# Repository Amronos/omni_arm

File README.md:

# Omni Arm

**_This is a work in progress and not usable currently._**

A universal robot arm featuring 3 robot grippers (parallel jaw, suction cup, and jamming) and 9 DOFS (including 3 for each gripper), allowing it to pickup objects of any kind as long as they have reasonable size and weight.

## Features

- 1 DOF for rotation on the x-axis.
- 3 DOFs for rotation on the y-axis.
- 2 DOFs for rotation on the z-axis.
- 3 different grippers: parallel jaw, suction cup, and jamming.
- Can pickup objects of any kind as long as they are of reasonable weight and size (size is not a limit for the suction cup gripper).
- Precise arm position control alongside position, velocity, load, and input voltage feedback from Waveshare servo motors.
- [ROS 2](https://docs.ros.org) support that uses [MoveIt 2](https://moveit.ai). (Coming Soon)

## Why Create This?

There are hardly any open-source and low-cost robot arms available out there that allow you to pikcup all sorts of objects with the use of various grippers.<br>
Most of the avilable robot arms also don't offer the kind of feedback and control one needs on the motors to perform complex kinematics and dynamics.<br>
This robot arm does all of that, making it perfect for my use-cases.

## Images

## Wiring Diagram

## BOM

| Item                                    | Unit Price | Quantity | Total Price | Links                                                                     |
| --------------------------------------- | ---------- | -------- | ----------- | ------------------------------------------------------------------------- |
| Waveshare SC15 Servo                    | $17.99     | 4        | $71.96      | https://www.waveshare.com/sc15-servo.htm                                  |
| Waveshare SC09 Servo                    | $8.99      | 4        | $35.96      | https://www.waveshare.com/sc09-servo.htm                                  |
| PCB                                     | $43.77     | 2        | $43.77      | https://jlpcb.com/                                                        |
| Xiao ESP32-C3                           | $5.71      | 1        | $5.71       | https://thinkrobotics.com/products/seeed-studio-xiao-esp32c3              |
| Dispo Van 20 ml Plastic Syringe         | $0.23      | 1        | $0.23       | https://www.amazon.in/DISPO-Plastic-Syringe-Medical-Purpose/dp/B09KS18BMY |
| Suction Cup Gripper for DIY Robot Arms  | $27.85     | 1        | $27.85      | https://thinkrobotics.com/products/suction-cup-gripper-for-diy-robot-arms |
| M2x9.5 Pan Head Self Tapping Screw      | —          | 10       | —           | —                                                                         |
| M2x6.5 Pan Head Self Tapping Screw      | —          | 10       | —           | —                                                                         |
| M3x8 Pan Head Self Tapping Screw        | —          | 4        | —           | —                                                                         |
| M3x10 Pan Head Self Tapping Screw       | —          | 2        | —           | —                                                                         |
| 2x50mm Stainless Steel Round Shaft Rods | —          | 2        | —           | —                                                                         |
| 3D Prints                               | —          | 1        | —           | https://github.com/Amronos/omni_arm/tree/main/CAD                         |
|                                         |            |          | $185.48     |                                                                           |

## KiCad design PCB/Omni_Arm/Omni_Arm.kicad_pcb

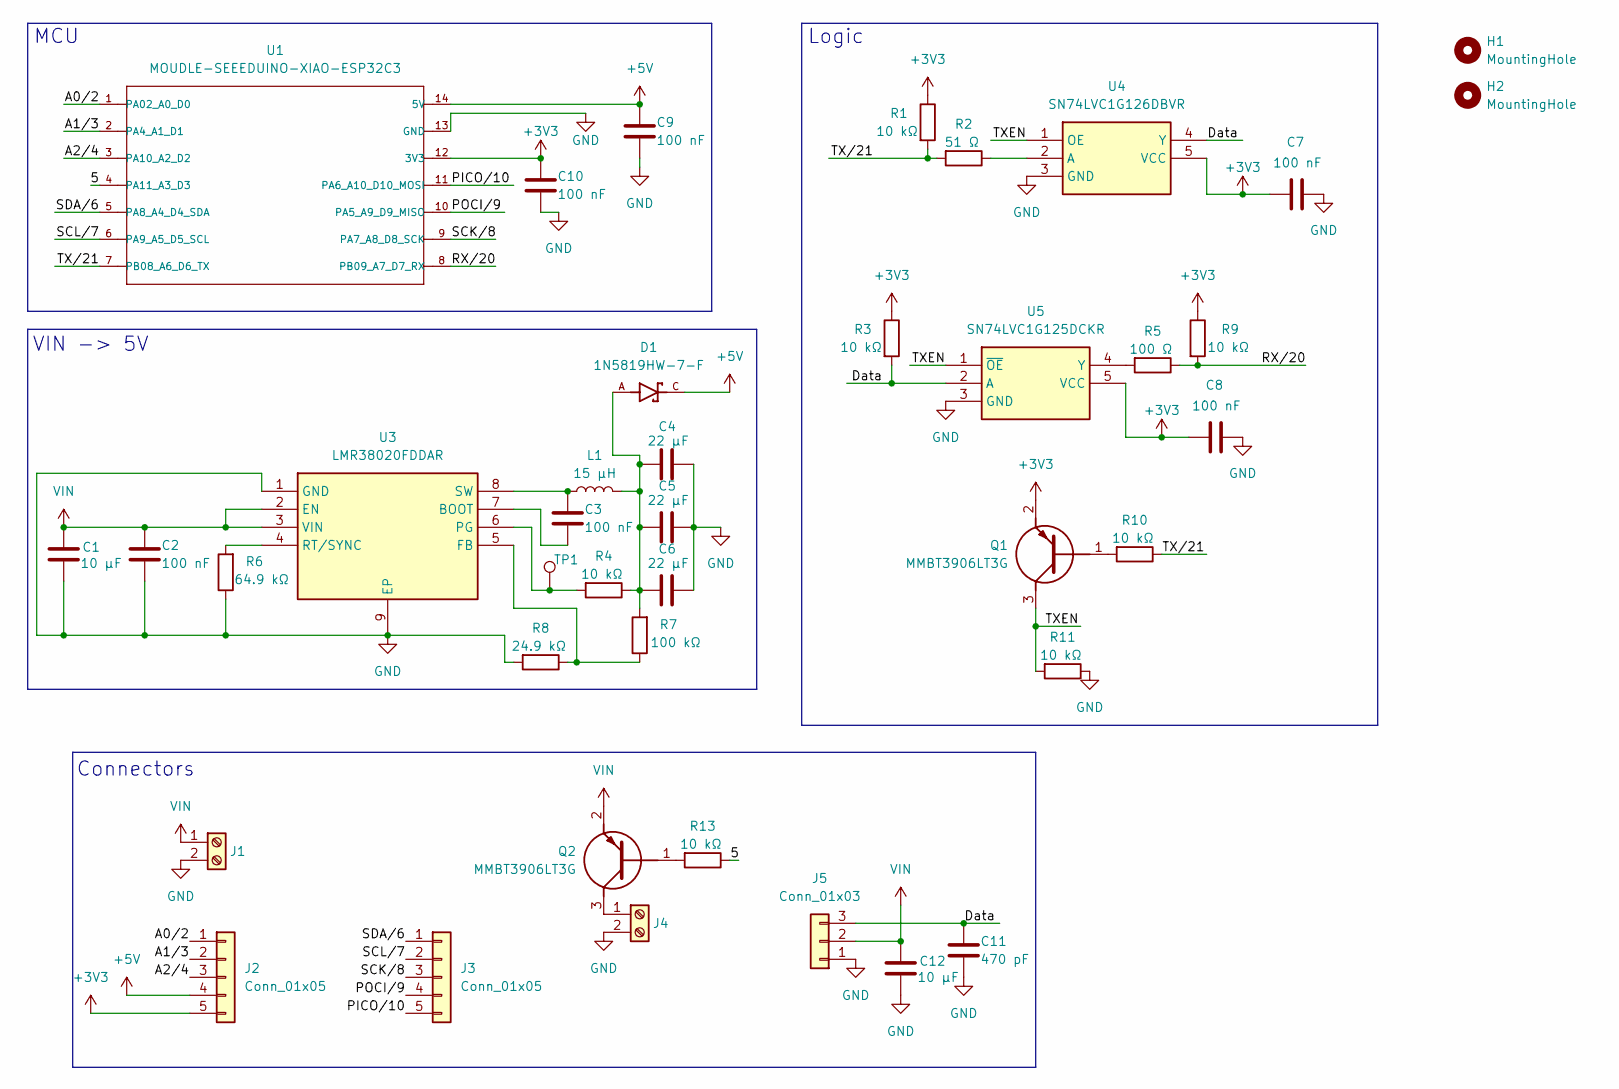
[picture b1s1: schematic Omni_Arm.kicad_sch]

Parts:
C1, C12: 10 µF; C_0805_2012Metric
C2, C3, C7, C8, C9, C10: 100 nF; C_0402_1005Metric
C4, C5, C6: 22 µF; C_0603_1608Metric
C11: 470 pF; C_0402_1005Metric
D1: 1N5819HW-7-F; SOD3715X145N
H1, H2: MountingHole; MountingHole_3.2mm_M3
J1, J4: Screw_Terminal_01x02; TerminalBlock_Xinya_XY308-2.54-2P_1x02_P2.54mm_Horizontal
J2, J3: Conn_01x05; PinHeader_1x05_P2.54mm_Vertical
J5: Conn_01x03; JST_EH_S3B-EH_1x03_P2.50mm_Horizontal
L1: 15 µH; INDPM102100X400N
Q1, Q2: MMBT3906LT3G; SOT96P237X111-3N; Mouser Part Number 863-MMBT3906LT3G
R1, R3, R4, R9, R10, R11, R13: 10 kΩ; R_0402_1005Metric
R2: 51 Ω; R_0402_1005Metric
R5: 100 Ω; R_0402_1005Metric
R6: 64.9 kΩ; R_0402_1005Metric
R7: 100 kΩ; R_0402_1005Metric
R8: 24.9 kΩ; R_0402_1005Metric
TP1: TestPoint; TestPoint_Pad_1.0x1.0mm
U1: MOUDLE-SEEEDUINO-XIAO-ESP32C3; XIAO-ESP32C3-SMD
U3: LMR38020FDDAR; SOIC127P600X170-9N
U4: SN74LVC1G126DBVR; SOT95P280X145-5N; Manufacturer_Part_Number SN74LVC1G126DBVR; Mouser Part Number 595-SN74LVC1G126DBVR
U5: SN74LVC1G125DCKR; SOT65P210X110-5N; Manufacturer_Part_Number SN74LVC1G125DCKR; Mouser Part Number 595-SN74LVC1G125DCKR

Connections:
+3V3: C7.1, C8.1, C10.1, J2.5, Q1.2 (E), R1.1, R3.1, R9.1, U1.12 (3V3), U4.5 (VCC), U5.5 (VCC)
+5V: C9.1, D1.C, J2.4, U1.14 (5V)
/5: R13.1, U1.4 (PA11_A3_D3)
/A0/2: J2.1, U1.1 (PA02_A0_D0)
/A1/3: J2.2, U1.2 (PA4_A1_D1)
/A2/4: J2.3, U1.3 (PA10_A2_D2)
/Data: C11.1, J5.3, R3.2, U4.4 (Y), U5.2 (A)
/PICO/10: J3.5, U1.11 (PA6_A10_D10_MOSI)
/POCI/9: J3.4, U1.10 (PA5_A9_D9_MISO)
/RX/20: R5.1, R9.2, U1.8 (PB09_A7_D7_RX)
/SCK/8: J3.3, U1.9 (PA7_A8_D8_SCK)
/SCL/7: J3.2, U1.6 (PA9_A5_D5_SCL)
/SDA/6: J3.1, U1.5 (PA8_A4_D4_SDA)
/TXEN: Q1.3 (C), R11.2, U4.1 (OE), U5.1 (~OE)
/TX/21: R1.2, R2.2, R10.1, U1.7 (PB08_A6_D6_TX)
GND: C1.2, C2.2, C4.2, C5.2, C6.2, C7.2, C8.2, C9.2, C10.2, C11.2, C12.2, J1.2, J4.2, J5.1, R6.1, R8.2, R11.1, U1.13 (GND), U3.1 (GND), U3.9 (EP), U4.3 (GND), U5.3 (GND)
unnamed: C4.1, C5.1, C6.1, D1.A, L1.2, R4.1, R7.2
unnamed: J4.1, Q2.3 (C)
unnamed: Q1.1 (B), R10.2
unnamed: Q2.1 (B), R13.2
unnamed: C3.2, U3.7 (BOOT)
unnamed: R7.1, R8.1, U3.5 (FB)
unnamed: R4.2, TP1.1, U3.6 (PG)
unnamed: R6.2, U3.4 (RT/SYNC)
unnamed: C3.1, L1.1, U3.8 (SW)
unnamed: R2.1, U4.2 (A)
unnamed: R5.2, U5.4 (Y)
VIN: C1.1, C2.1, C12.1, J1.1, J5.2, Q2.2 (E), U3.2 (EN), U3.3 (VIN)

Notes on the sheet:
Logic
VIN -> 5V
Connectors
MCU

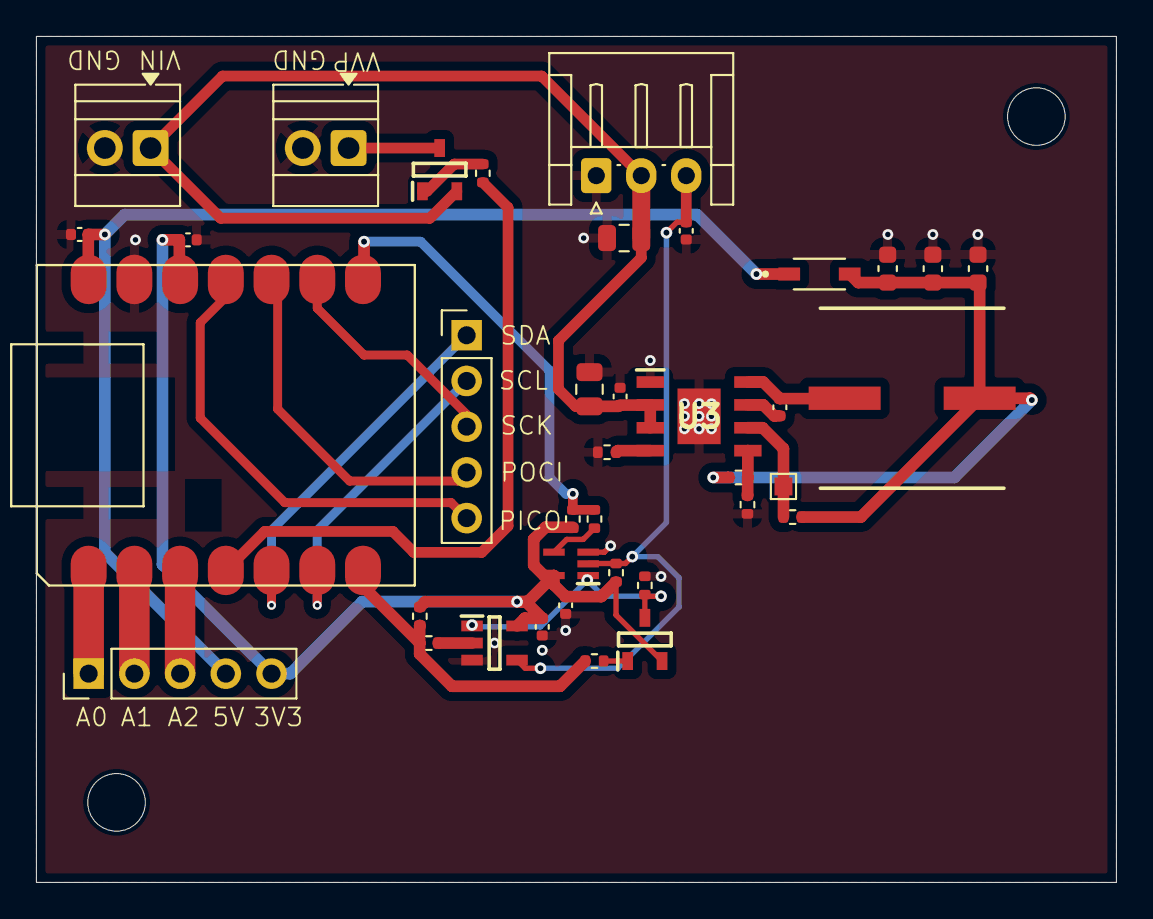
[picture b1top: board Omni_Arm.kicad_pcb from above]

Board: 2 copper layers, 60.0 x 47.0 mm, 40 parts (0 on the bottom side), 28 nets.

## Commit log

2025-07-10 Add z-axis servo motor
2025-07-13 Complete base
2025-07-18 Complete housing for y-axis motor
2025-07-19 Change the idea a bit
2025-07-26 Complete Y-Axis_2
2025-07-27 Complete housing for x-axis motor
2025-07-27 Complete housing for Z-Axis_2
2025-07-30 Complete parallel gripper and add another y-axis DOF
2025-07-31 Complete 3D model for printing and update README.md
2025-07-31 Add firmware and wiring diagram
2025-08-09 Add custom PCB
2025-08-09 Fix BOM and path
